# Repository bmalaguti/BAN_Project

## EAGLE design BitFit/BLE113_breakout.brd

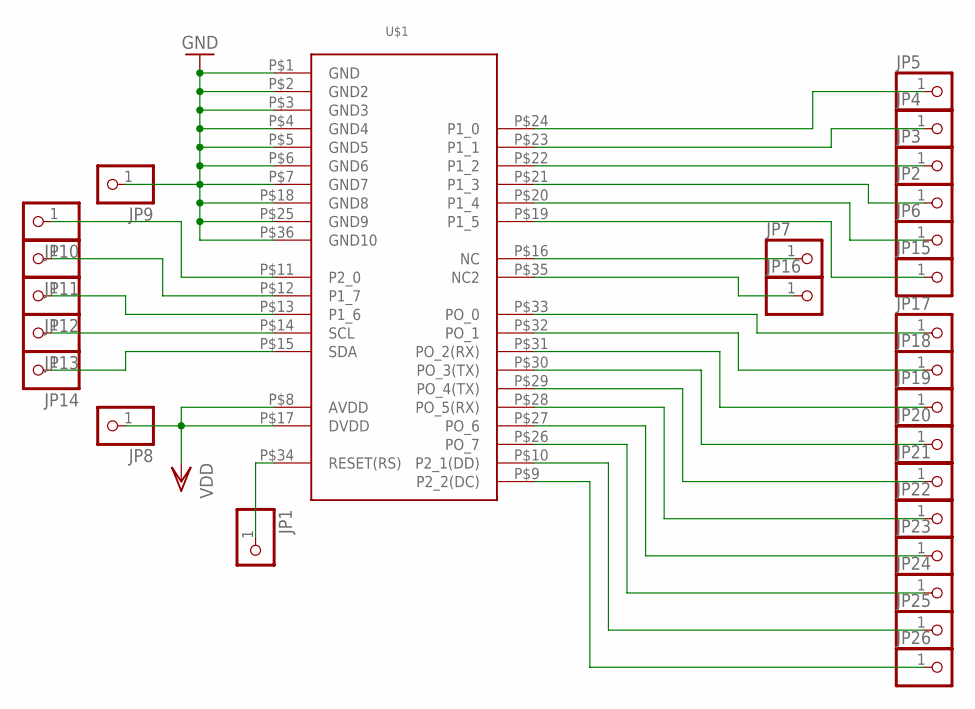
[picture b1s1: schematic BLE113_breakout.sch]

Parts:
JP1, JP2, JP3, JP4, JP5, JP6, JP7, JP8, JP9, JP10, JP11, JP12, JP13, JP14, JP15, JP16, JP17, JP18, JP19, JP20, JP21, JP22, JP23, JP24, JP25, JP26: PINHD-1X1; 1X01
U$1: BLE113-A; BLUETOOTHNS

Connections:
GND: JP9.1, U$1.P$1 (GND), U$1.P$2 (GND2), U$1.P$3 (GND3), U$1.P$4 (GND4), U$1.P$5 (GND5), U$1.P$6 (GND6), U$1.P$7 (GND7), U$1.P$18 (GND8), U$1.P$25 (GND9), U$1.P$36 (GND10)
unnamed: JP5.1, U$1.P$24 (P1_0)
unnamed: JP4.1, U$1.P$23 (P1_1)
unnamed: JP3.1, U$1.P$22 (P1_2)
unnamed: JP2.1, U$1.P$21 (P1_3)
unnamed: JP6.1, U$1.P$20 (P1_4)
unnamed: JP15.1, U$1.P$19 (P1_5)
unnamed: JP1.1, U$1.P$34 (RESET(RS))
unnamed: JP7.1, U$1.P$16 (NC)
unnamed: JP16.1, U$1.P$35 (NC2)
unnamed: JP17.1, U$1.P$33 (PO_0)
unnamed: JP18.1, U$1.P$32 (PO_1)
unnamed: JP19.1, U$1.P$31 (PO_2(RX))
unnamed: JP20.1, U$1.P$30 (PO_3(TX))
unnamed: JP21.1, U$1.P$29 (PO_4(TX))
unnamed: JP22.1, U$1.P$28 (PO_5(RX))
unnamed: JP23.1, U$1.P$27 (PO_6)
unnamed: JP24.1, U$1.P$26 (PO_7)
unnamed: JP25.1, U$1.P$10 (P2_1(DD))
unnamed: JP26.1, U$1.P$9 (P2_2(DC))
unnamed: JP10.1, U$1.P$11 (P2_0)
unnamed: JP11.1, U$1.P$12 (P1_7)
unnamed: JP12.1, U$1.P$13 (P1_6)
unnamed: JP13.1, U$1.P$14 (SCL)
unnamed: JP14.1, U$1.P$15 (SDA)
VDD: JP8.1, U$1.P$8 (AVDD), U$1.P$17 (DVDD)

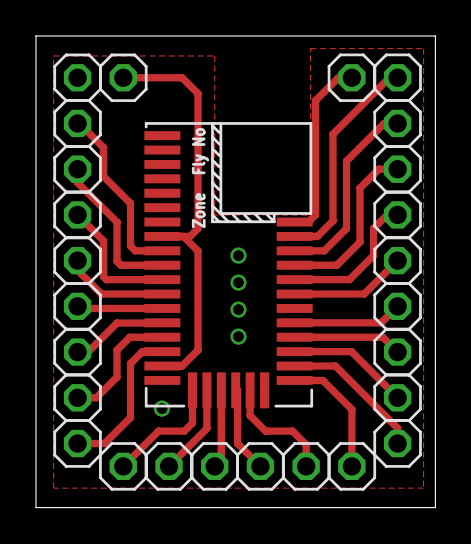
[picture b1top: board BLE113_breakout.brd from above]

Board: 2 copper layers, 22.2 x 26.2 mm, 27 parts (0 on the bottom side), 26 nets.

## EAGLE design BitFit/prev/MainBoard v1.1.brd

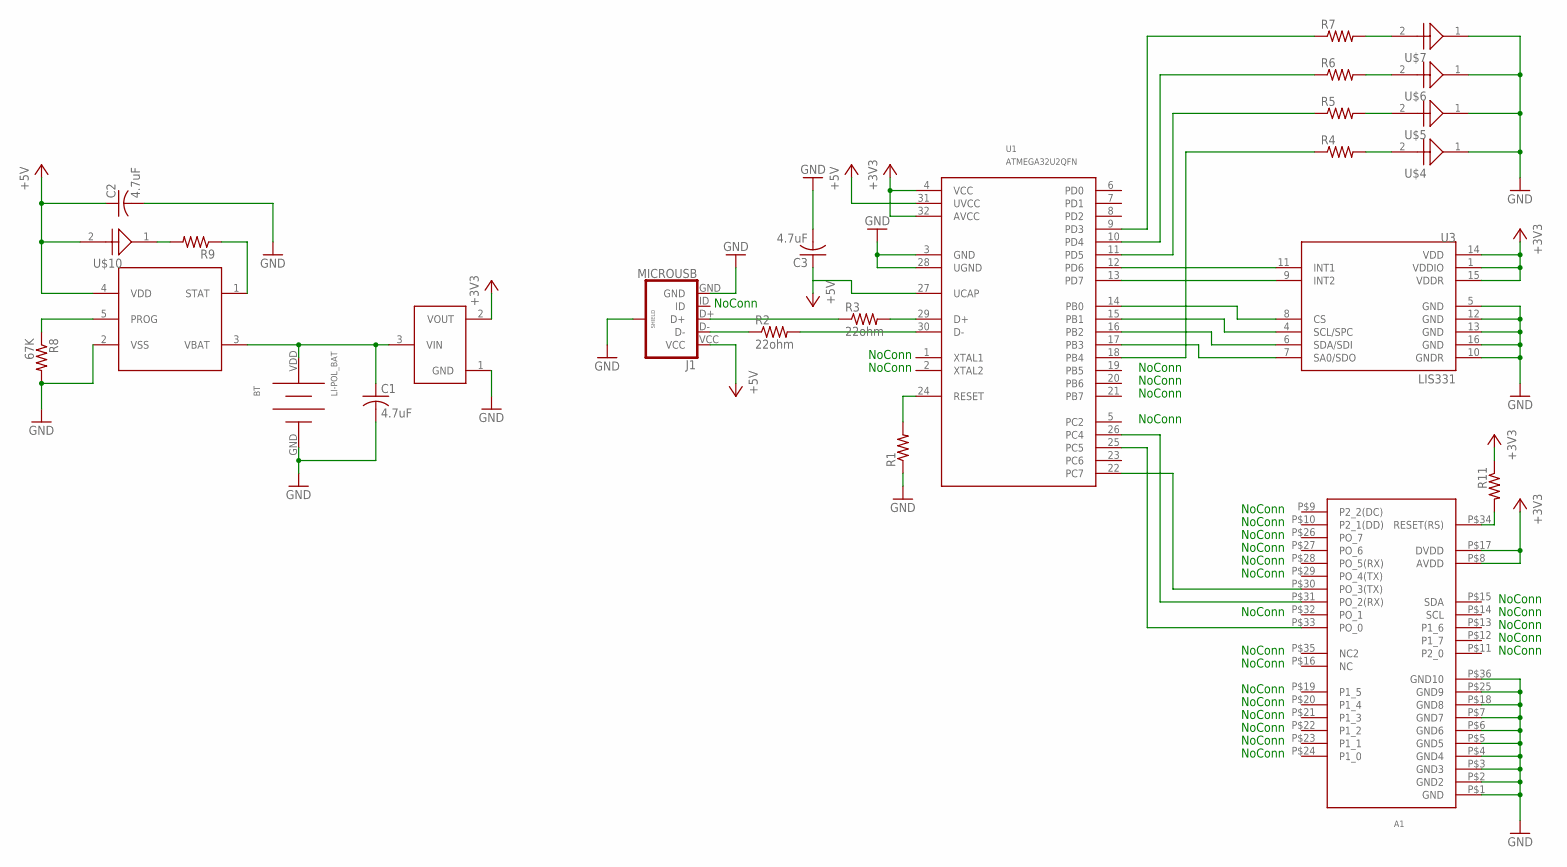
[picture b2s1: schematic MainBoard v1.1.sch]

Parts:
A1: BLE113-A; BLUETOOTHNS
BT: LI-POL_BAT; LI-POLY_28
C1, C2, C3: 4.7uF; C0402
J1: MICROUSB
R1, R4, R5, R6, R7, R9, R11: R-US_R0402; R0402
R2, R3: 22ohm; R0402
R8: 67K; R0402
U1: ATMEGA32U2QFN; QFN-32
U2: MCP738312; SOT23-5
U3: LIS331; LGA16-3MM
U5: REGULATOR; SOT23-3
U$4, U$5, U$6, U$7, U$10: LED_0402; R0402

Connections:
+3V3: A1.P$8 (AVDD), A1.P$17 (DVDD), R11.1, U1.4 (VCC), U1.32 (AVCC), U3.1 (VDDIO), U3.14 (VDD), U3.15 (VDDR), U5.2 (VOUT)
+5V: C2.1, C3.1, J1.VCC, U1.27 (UCAP), U1.31 (UVCC), U2.4 (VDD), U$10.2
GND: A1.P$1 (GND), A1.P$2 (GND2), A1.P$3 (GND3), A1.P$4 (GND4), A1.P$5 (GND5), A1.P$6 (GND6), A1.P$7 (GND7), A1.P$18 (GND8), A1.P$25 (GND9), A1.P$36 (GND10), BT.GND, C1.2, C2.2, C3.2, J1.GD1 (SHIELD), J1.GD2 (SHIELD), J1.GD3 (SHIELD), J1.GD4 (SHIELD), J1.GND, R1.1, R8.2, U1.3 (GND), U1.28 (UGND), U2.2 (VSS), U3.5 (GND), U3.10 (GNDR), U3.12 (GND), U3.13 (GND), U3.16 (GND), U5.1 (GND), U$4.1, U$5.1, U$6.1, U$7.1
unnamed: R3.2, U1.29 (D+)
unnamed: R2.2, U1.30 (D-)
unnamed: R1.2, U1.24 (RESET)
unnamed: R4.2, U$4.2
unnamed: R5.2, U$5.2
unnamed: R6.2, U$6.2
unnamed: R7.2, U$7.2
unnamed: J1.D+, R3.1
unnamed: J1.D-, R2.1
unnamed: BT.VDD, C1.1, U2.3 (VBAT), U5.3 (VIN)
unnamed: A1.P$34 (RESET(RS)), R11.2
unnamed: R8.1, U2.5 (PROG)
unnamed: R9.1, U2.1 (STAT)
unnamed: R9.2, U$10.1
unnamed: U1.12 (PD6), U3.11 (INT1)
unnamed: R4.1, U1.18 (PB4)
unnamed: R6.1, U1.10 (PD4)
unnamed: U1.15 (PB1), U3.4 (SCL/SPC)
unnamed: U1.14 (PB0), U3.8 (CS)
unnamed: R5.1, U1.11 (PD5)
unnamed: U1.16 (PB2), U3.6 (SDA/SDI)
unnamed: U1.17 (PB3), U3.7 (SA0/SDO)
unnamed: U1.13 (PD7), U3.9 (INT2)
unnamed: A1.P$31 (PO_2(RX)), U1.26 (PC4)
unnamed: A1.P$30 (PO_3(TX)), U1.22 (PC7)
unnamed: A1.P$33 (PO_0), U1.25 (PC5)
unnamed: R7.1, U1.9 (PD3)

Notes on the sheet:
NoConn

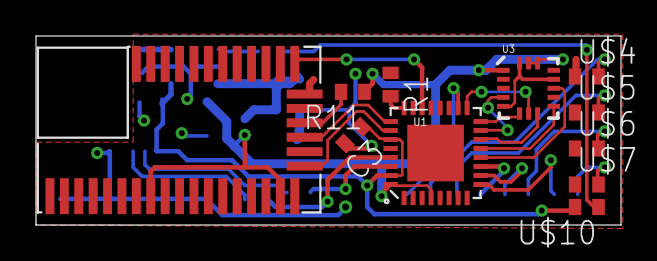
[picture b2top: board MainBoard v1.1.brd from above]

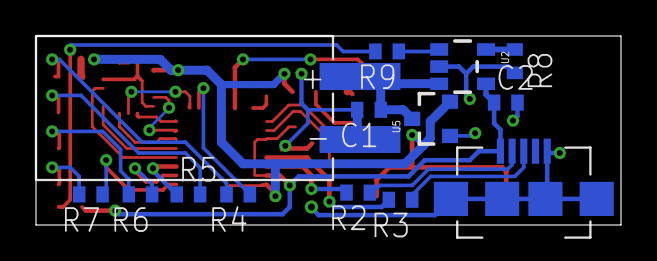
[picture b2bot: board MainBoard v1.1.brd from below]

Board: 2 copper layers, 32.5 x 10.5 mm, 25 parts (14 on the bottom side), 30 nets.

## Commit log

2015-03-01 :lollipop: Added .gitattributes & .gitignore files
2015-03-01 v15.9.0
    Includes Eagle Board, Schematic, and Library.
2015-03-09 Version 1.0
    Finished version 1.0 of layout.
2015-03-09 Version 1.1
    Fixed VCAP
2015-03-12 Version 1.3
    Silkscreen Added
2015-03-12 File Clean Up
    Removed Eagle Automatic Backups
2015-03-12 Revert "File Clean Up"
    This reverts commit 10255cb1ed82fce6ed301fa510a3af56dd328698.
2015-03-12 File Clean Up v2
2015-03-12 Revert "Revert "File Clean Up""
    This reverts commit 91857feefb73527831a93d79419fa160ec2c3017.
2015-03-12 Version 0.5
2015-03-12 Lib Added
    Library's for parts added to lib folder.
2015-03-12 Previous Moved
    Previous versions of the board and schematic were moved to organize the
    folder.
2015-03-26 Version 1.4
    Adds BLE113, Changes to MainBoard
2015-03-26 Version 1.4.1
    Reconfigure Bluetooth and Reset
2015-03-26 Version 1.4.2
    Add Arduino BLE113 files, minor Mainboard fixes
2015-03-30 Version 1.4.3
    Clean Directory
2015-04-02 Version 1.4.4
    Add accelDemo for breadboarded Arduino Uno. Eagle Up files generated for
    3D Model.
2015-04-02 Version 1.4.5
    Added library for accelDemo. Modified from Adafruit nrF8001
2015-04-09 Version 1.4.6
    Add BLEFirmware.
2015-04-17 Version 1.4.7
    Add ota BLE113 Firmware, Modify 38400_noflow_wake16
2015-04-21 Version 1.4.8
    OTA Update
2015-04-22 Version 1.4.9
    Update OTA

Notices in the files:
parts and their libraries:
SparkFun-Sensors: Licensing: Creative Commons ShareAlike 4.0 International - https://creativecommons.org/licenses/by-sa/4.0
